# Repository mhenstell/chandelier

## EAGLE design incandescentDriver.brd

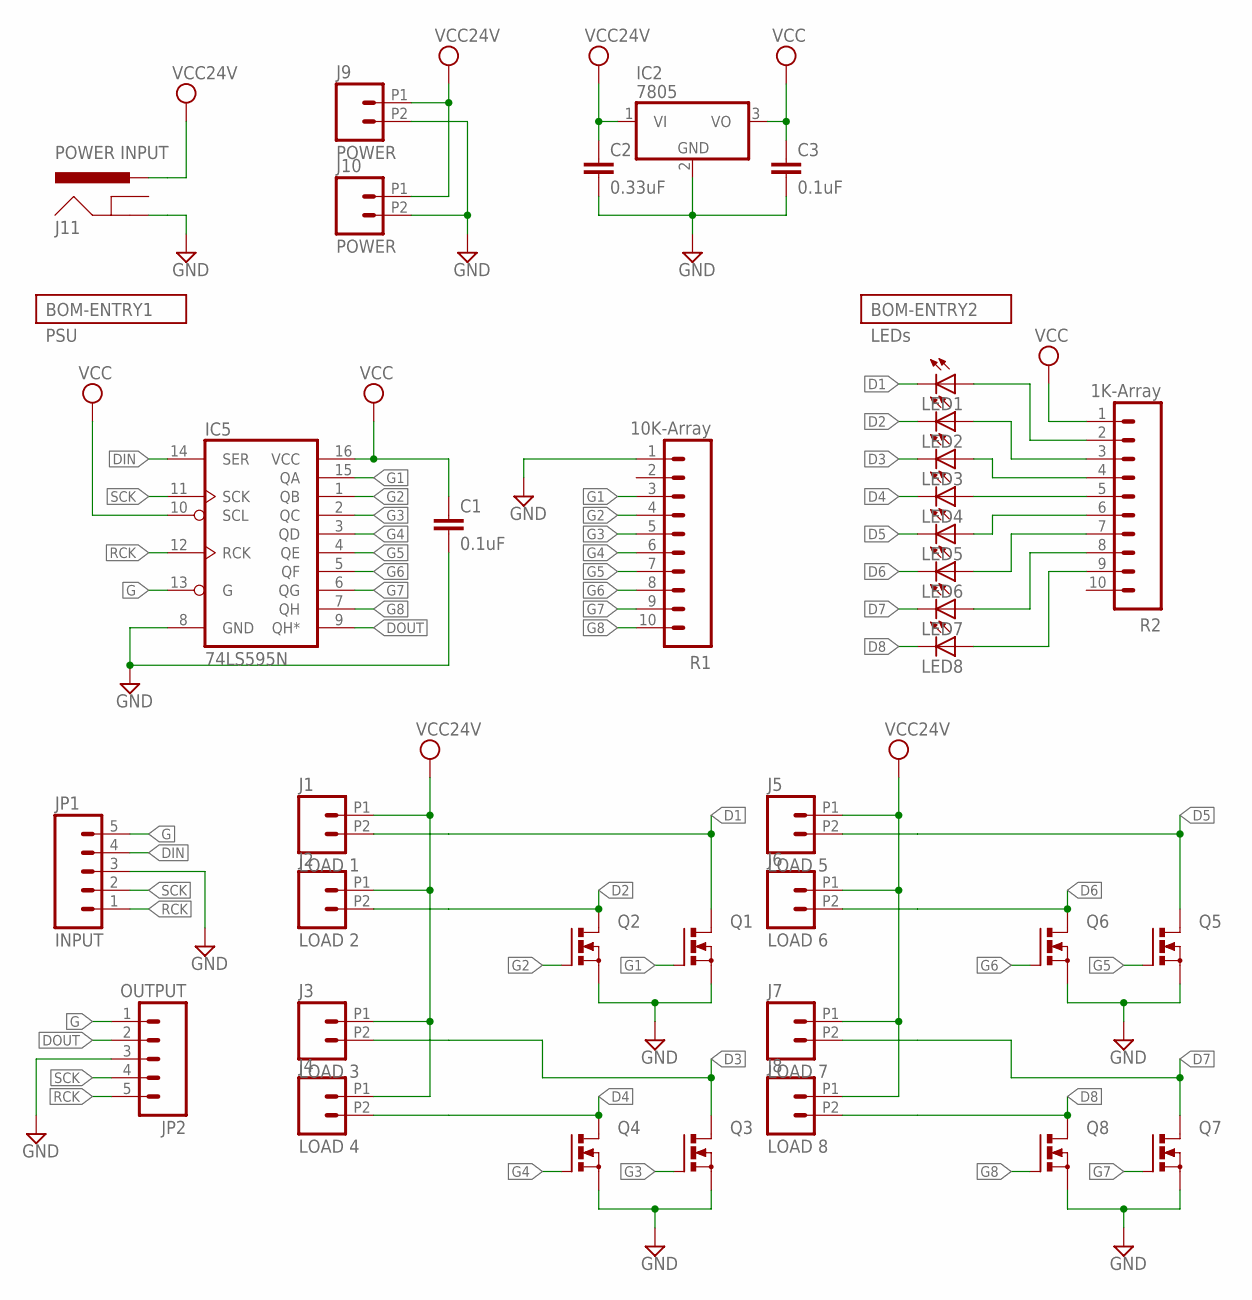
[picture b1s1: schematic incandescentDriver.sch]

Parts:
C1, C3: 0.1uF; CAP-PTH-SMALL; PARTNO SR295E104MAR
C2: 0.33uF; CAP-PTH-SMALL; PARTNO FK24X7R1H334K
IC2: 7805; TO220V; PARTNO NCP7805TG
IC5: 74LS595N; DIL16; PARTNO SN74HC164N
J1: LOAD 1; 1X02-5.08-SCREWTERM; PARTNO OSTTC022162
J2: LOAD 2; 1X02-5.08-SCREWTERM; PARTNO OSTTC022162
J3: LOAD 3; 1X02-5.08-SCREWTERM; PARTNO OSTTC022162
J4: LOAD 4; 1X02-5.08-SCREWTERM; PARTNO OSTTC022162
J5: LOAD 5; 1X02-5.08-SCREWTERM; PARTNO OSTTC022162
J6: LOAD 6; 1X02-5.08-SCREWTERM; PARTNO OSTTC022162
J7: LOAD 7; 1X02-5.08-SCREWTERM; PARTNO OSTTC022162
J8: LOAD 8; 1X02-5.08-SCREWTERM; PARTNO OSTTC022162
J9, J10: POWER; 1X02-5.08-SCREWTERM; PARTNO OSTTC022162
J11: POWER INPUT; POWER_JACK_PTH_LOCK; PARTNO PJ-202A
JP1: INPUT; 1X05_LOCK; PARTNO M20-9960545
JP2: OUTPUT; 1X05_LOCK; PARTNO M20-9960545
LED1, LED2, LED3, LED4, LED5, LED6, LED7, LED8: LED5MM
Q1, Q2, Q3, Q4, Q5, Q6, Q7, Q8: PMOSFET_NTO220BV; TO220BV; PARTNO FQP13N10L
R1: 10K-Array; 1X10_LOCK; PARTNO L101S103LF
R2: 1K-Array; 1X10_LOCK; PARTNO 4609X-101-102LF

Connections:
D1: J1.P2 (1), LED1.K (C), Q1.D
D2: J2.P2 (1), LED2.K (C), Q2.D
D3: J3.P2 (1), LED3.K (C), Q3.D
D4: J4.P2 (1), LED4.K (C), Q4.D
D5: J5.P2 (1), LED5.K (C), Q5.D
D6: J6.P2 (1), LED6.K (C), Q6.D
D7: J7.P2 (1), LED7.K (C), Q7.D
D8: J8.P2 (1), LED8.K (C), Q8.D
DIN: IC5.14 (SER), JP1.4
DOUT: IC5.9 (QH*), JP2.2
G: IC5.13 (G), JP1.5, JP2.1
G1: IC5.15 (QA), Q1.G, R1.3
G2: IC5.1 (QB), Q2.G, R1.4
G3: IC5.2 (QC), Q3.G, R1.5
G4: IC5.3 (QD), Q4.G, R1.6
G5: IC5.4 (QE), Q5.G, R1.7
G6: IC5.5 (QF), Q6.G, R1.8
G7: IC5.6 (QG), Q7.G, R1.9
G8: IC5.7 (QH), Q8.G, R1.10
GND: C1.2, C2.2, C3.2, IC2.2 (GND), IC5.8 (GND), J9.P2 (1), J10.P2 (1), J11.GND, JP1.3, JP2.3, Q1.S, Q2.S, Q3.S, Q4.S, Q5.S, Q6.S, Q7.S, Q8.S, R1.1
unnamed: LED1.A, R2.2
unnamed: LED2.A, R2.3
unnamed: LED3.A, R2.4
unnamed: LED4.A, R2.5
unnamed: LED5.A, R2.6
unnamed: LED6.A, R2.7
unnamed: LED7.A, R2.8
unnamed: LED8.A, R2.9
RCK: IC5.12 (RCK), JP1.1, JP2.5
SCK: IC5.11 (SCK), JP1.2, JP2.4
VCC: C1.1, C3.1, IC2.3 (VO), IC5.10 (SCL), IC5.16 (VCC), R2.1
VCC24V: C2.1, IC2.1 (VI), J1.P1 (2), J2.P1 (2), J3.P1 (2), J4.P1 (2), J5.P1 (2), J6.P1 (2), J7.P1 (2), J8.P1 (2), J9.P1 (2), J10.P1 (2), J11.PWR

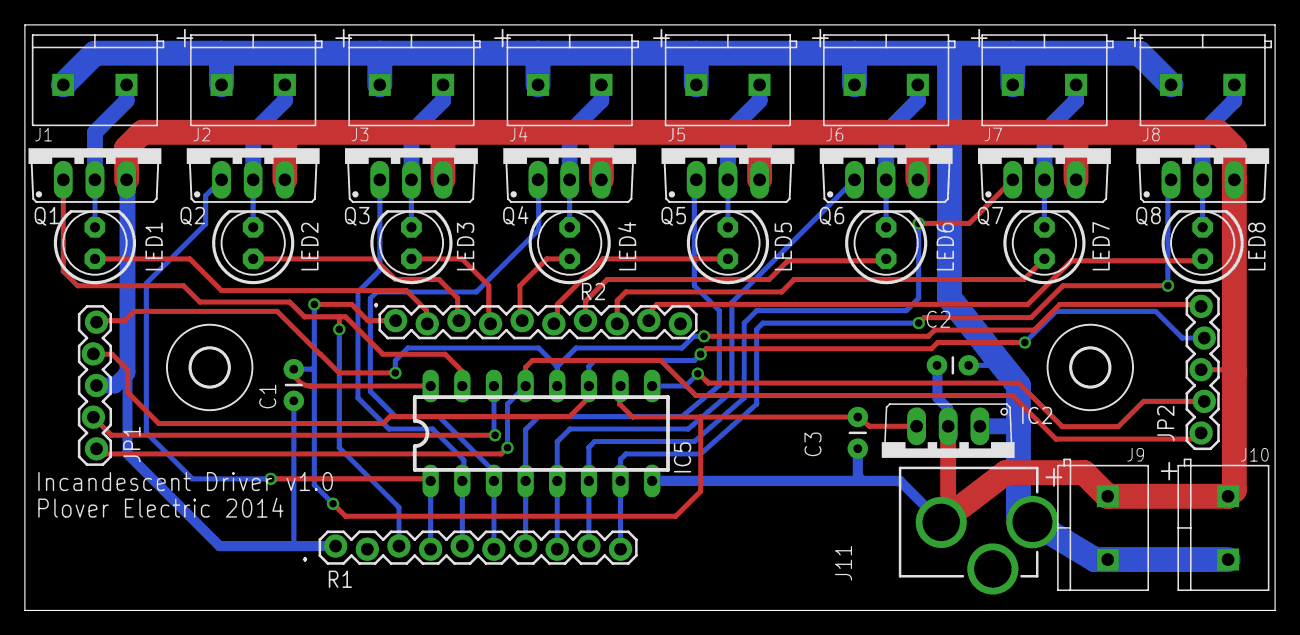
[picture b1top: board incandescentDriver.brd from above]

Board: 2 copper layers, 100.3 x 47.0 mm, 38 parts (0 on the bottom side), 32 nets.

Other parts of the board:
U$1, U$2: 3,0

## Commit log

2014-06-11 updated incandescent driver to 1.0
2014-06-23 removing incandescentdriver

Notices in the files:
parts and their libraries:
SparkFun-DigitalIC: Licensing: CC v3.0 Share-Alike You are welcome to use this library for commercial purposes.
bom: Copyright (C) 2010, Bob Starr
